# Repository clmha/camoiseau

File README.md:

# camoiseau
Firmware for the Camoiseau bird camera. Camoiseau automatically captures images of birds (or any wild life).

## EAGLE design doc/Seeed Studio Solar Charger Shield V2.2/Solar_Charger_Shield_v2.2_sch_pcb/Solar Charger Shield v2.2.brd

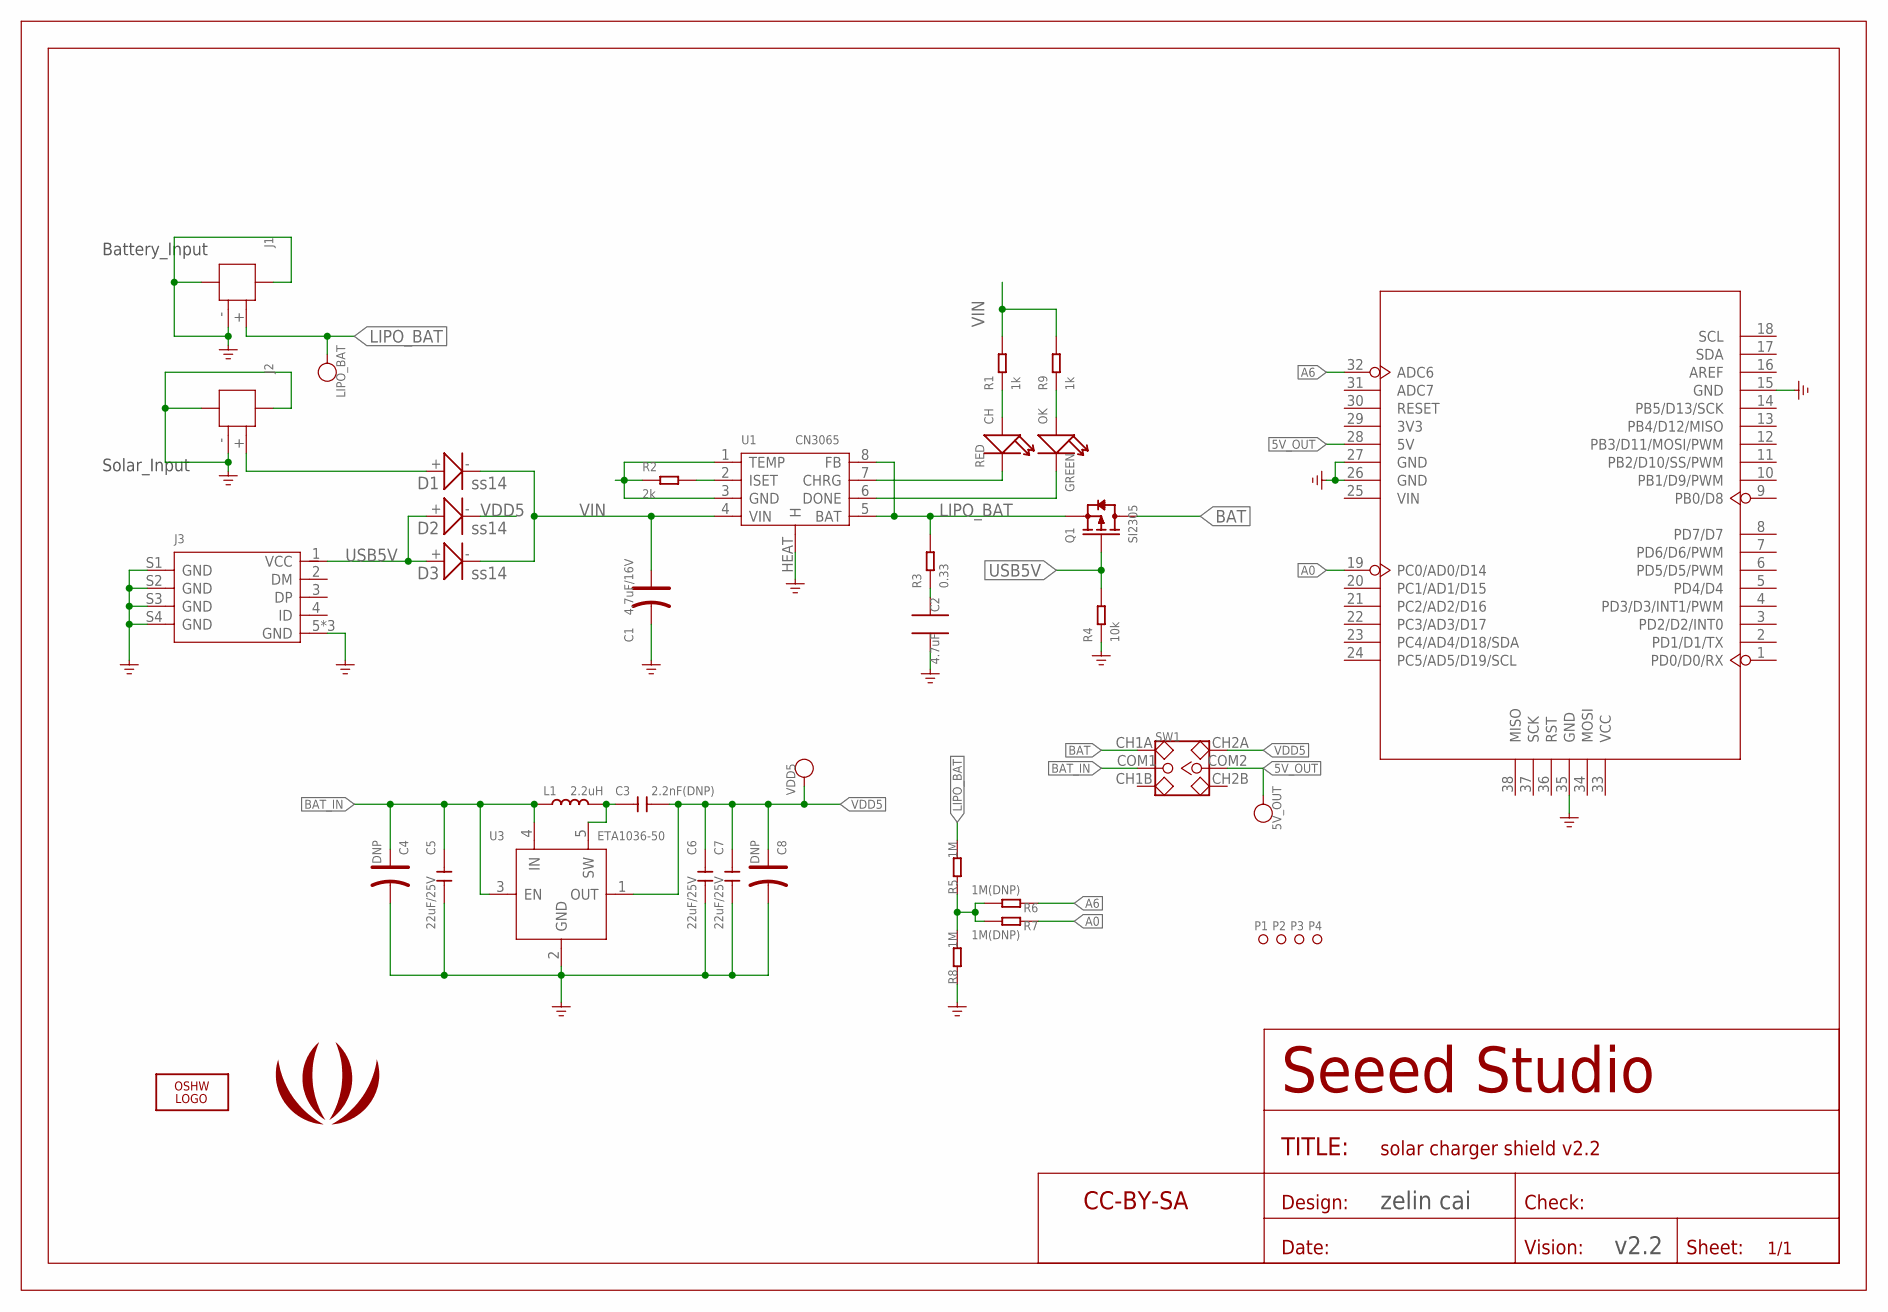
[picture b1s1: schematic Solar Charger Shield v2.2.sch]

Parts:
5V_OUT: PAD-TEST-POINT'4545'; TP-D45MIL
C1: 4.7uF/16V; AVX_A
C2: 4.7uF; 0805
C3: 2.2nF(DNP); C0603
C4, C8: DNP; AVX-A
C5, C6, C7: 22uF/25V; C0805
CH: RED; LED-0603
D1, D2, D3: ss14; D2010
J1, J2: JST-2P-SMD'2.0'; 2P-SMD-2.0-90D
J3: USB-MICRO-5P'5+4P'; 5+4P-SMD-0.65-B
L1: 2.2uH; L0630
LIPO_BAT: PAD-TEST-POINT'4545'; TP-D45MIL
LOGO1: LOGO-OSHW-FILLX0200-NT; OSHW_FILLX200_NOTEXT
OK: GREEN; LED-0603
P1, P2, P3, P4: PAD-MARK'ANNULAR'; ROUND-MARK-1.0
Q1: SI2305; SOT-23
R1, R9: 1k; R0603
R2: 2k; R0603
R3: 0.33; R0603
R4: 10k; R0603
R5, R8: 1M; 0603
R6, R7: 1M(DNP); 0603
SW1: SWITCH-2CH-6P'90D'; 6P-2CH-2.54-L9.0*W3.5*H3.2-90D
U1: CN3065; DFN-8
U2: ARDUINO-38P'WITH-SILK'; ARDUINO-DIM-WITH-SILK
U3: ETA1036-50; SOT23-5
U$1: LOGO-SEEEDSTUDIO-SILK; LOGO_SILK
U$2: SEEEDSTUDIO-OPEN-SCH-FRAME; SEEEDSTUDIO-PCB-FRAME
VDD5: PAD-TEST-POINT'4545'; TP-D45MIL

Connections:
5V_OUT: 5V_OUT.T, SW1.COM2, U2.28 (5V)
A0: R7.1, U2.19 (PC0/AD0/D14)
A6: R6.1, U2.32 (ADC6)
BAT: Q1.3 (D), SW1.CH1A
BAT_IN: C4.+, C5.1, L1.1, SW1.COM1, U3.3 (EN), U3.4 (IN)
GND: C1.-, C2.2, C4.-, C5.2, C6.2, C7.2, C8.-, J1.3, J1.4, J1.- (2), J2.3, J2.4, J2.- (2), J3.5 (GND), J3.S1 (GND), J3.S2 (GND), J3.S3 (GND), J3.S4 (GND), J3.S5 (GND), J3.S6 (GND), R2.1, R4.1, R8.1, U1.1 (TEMP), U1.3 (GND), U1.HEAT (H), U2.15 (GND), U2.26 (GND), U2.27 (GND), U2.35 (GND), U3.2 (GND)
LIPO_BAT: J1.+ (1), LIPO_BAT.T, Q1.2 (S), R3.2, R5.2, U1.5 (BAT), U1.8 (FB)
unnamed: R5.1, R6.2, R7.2, R8.2
unnamed: C3.1, L1.2, U3.5 (SW)
unnamed: D1.+, J2.+ (1)
unnamed: R2.2, U1.2 (ISET)
unnamed: CH.-, U1.7 (CHRG)
unnamed: CH.+, R1.1
unnamed: OK.-, U1.6 (DONE)
unnamed: OK.+, R9.1
unnamed: C2.1, R3.1
USB5V: D2.+, D3.+, J3.1 (VCC), Q1.1 (G), R4.2
VDD5: C3.2, C6.1, C7.1, C8.+, D2.-, SW1.CH2A, U3.1 (OUT), VDD5.T
VIN: C1.+, D1.-, D3.-, R1.2, R9.2, U1.4 (VIN)

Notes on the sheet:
Solar_Input
Battery_Input
zelin cai
v2.2

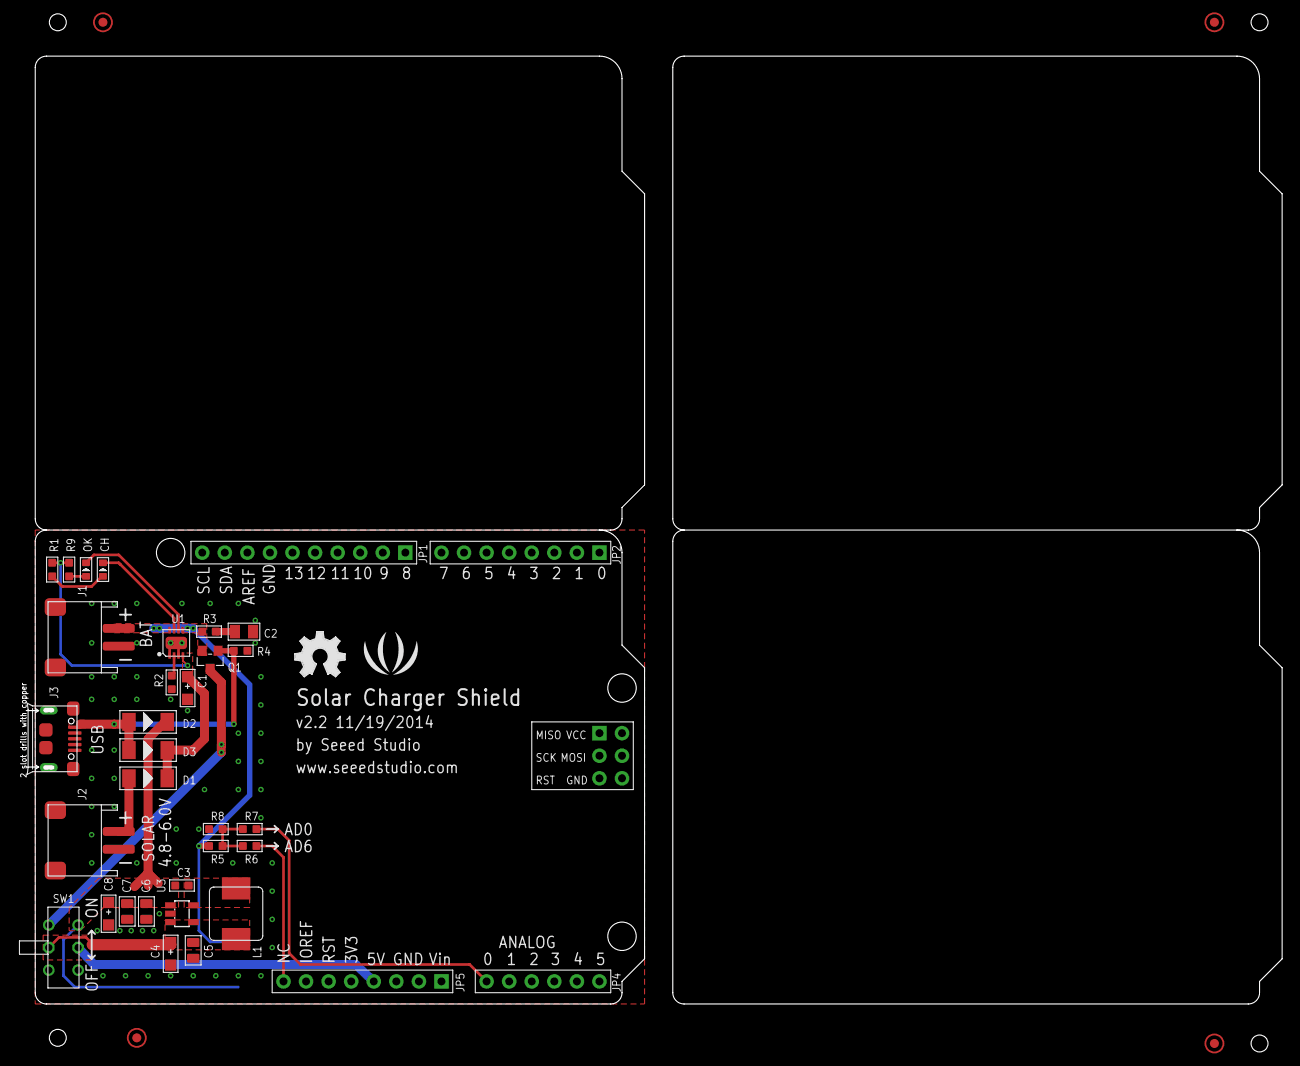
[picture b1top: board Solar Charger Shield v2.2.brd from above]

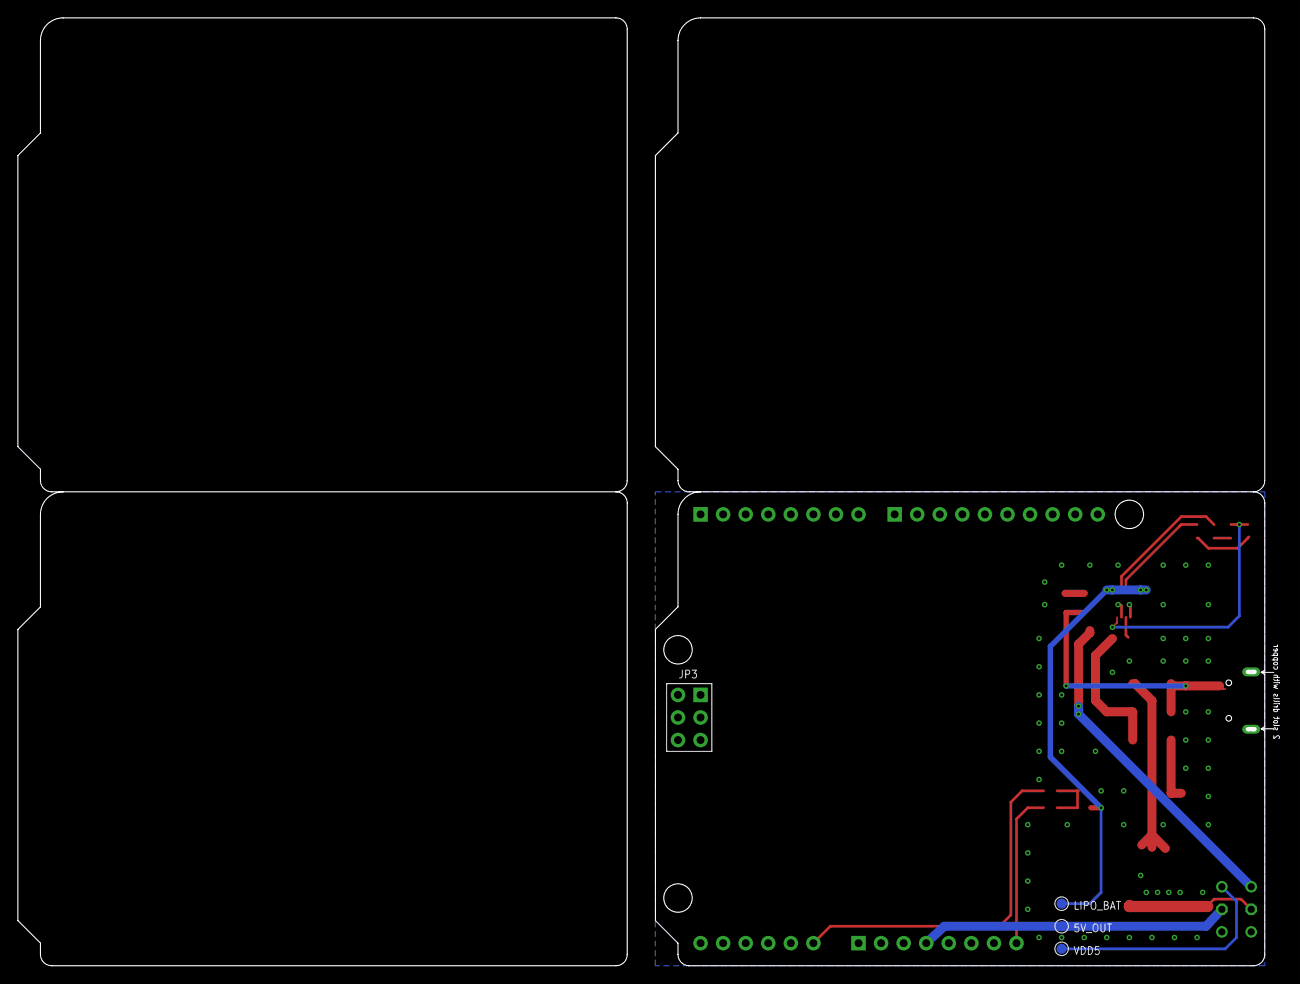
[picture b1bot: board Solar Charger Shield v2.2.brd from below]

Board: 2 copper layers, 141.8 x 106.2 mm, 41 parts (3 on the bottom side), 19 nets.

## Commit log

2018-12-24 Import of SVN Rev. 25
    We are moving from SVN to Git, this revision moves everything "as is" into the new Git repository.
2018-12-25 Removes SVN Keywords
2018-12-25 Removal of Low Power Mode
    The low power mode sections did not seem to work properly and should be investigated separately.
2018-12-26 Removes source files from the "doc" folder
    This was confusing Eclipse's parser.
2018-12-26 Removes source files from the ArduCAM folder and removes Arduino-ism from the main file (e.g. functions need to be properly declared).
    Takes also the opportunity to remove the revision of the Arduino IDE used and of the AVRBoard.

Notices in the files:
parts and their libraries:
moudle-new: This work is licensed under the Creative Commons Attribution 4.0 International License.
To view a copy of this license,visit:
http://creativecommons.org/licenses/by-sa/4.0
moudle-new: CC-BY-SA
